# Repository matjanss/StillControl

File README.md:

# StillControl
Simple Arduino Nano based solid state relay control hardware and software

Repository will be updated intermittently.

Please refer to the "Hardware" folder for the PCB & license information, software folder contains a VSCode project.

https://youtu.be/iHSRMQVA5wc

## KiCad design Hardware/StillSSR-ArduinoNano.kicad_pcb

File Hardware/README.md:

# StillControl PCB v1.0
Simple Arduino Nano based solid state relay control hardware and software

---

The PCB is a relatively simple breakout board for an Arduino Nano, exposing a number of interfaces in JST PH (2.00mm) connectors and standard 2.54mm pin Headers:

- Footprint for an Arduino Nano V3 with (optional/additional) breakout pin row exposed.
- 3 potentiometers (with filter caps & resistor)
- 3 buffered and somewhat protected SSR outputs
- I2C for ie. display or other peripherals
- I2C header for a BMP388/390 barometer
- 1-Wire interface for temperature sensors
- Buzzer
- Error led connector
- On board 5V regulator, needs 9-12V

Repository will be updated when board is tested, updates to be done in v1.1
Hardware is licensed under Creative Commons NC BY SA.

JLCPCB Production files: StillSSR-Arduinonano.zip

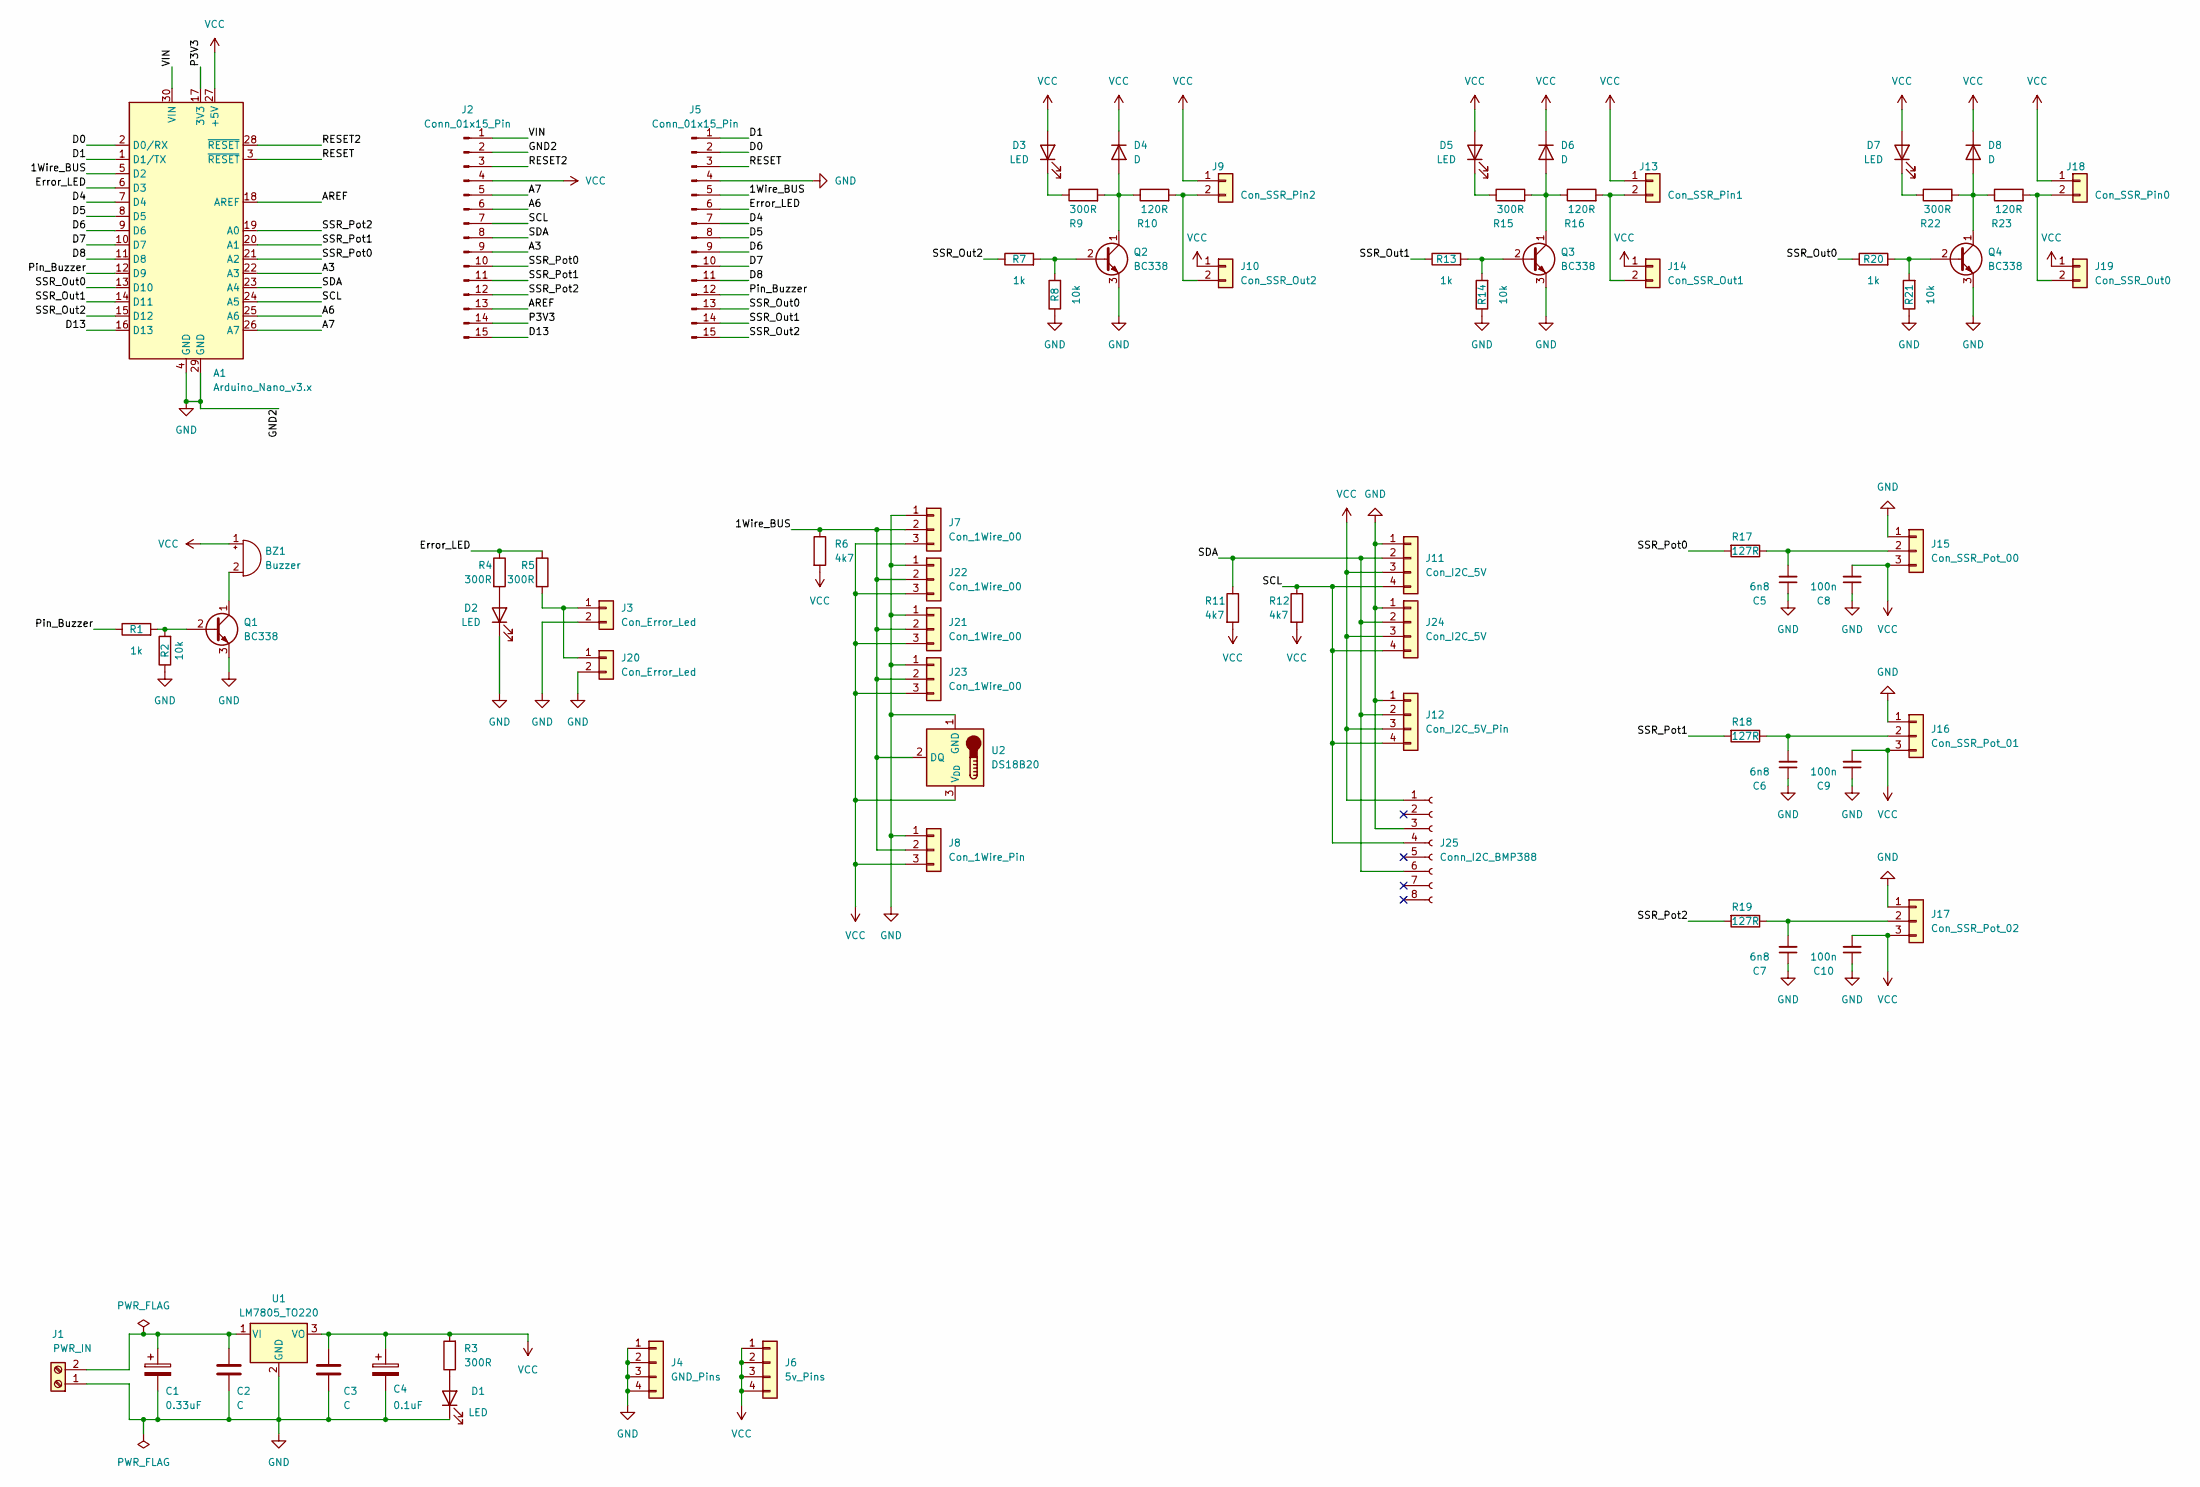
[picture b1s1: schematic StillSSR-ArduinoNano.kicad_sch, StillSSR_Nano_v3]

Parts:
A1: Arduino_Nano_v3.x; Arduino_Nano
BZ1: Buzzer; Buzzer_12x9.5RM7.6
C1: 0.33uF; CP_Radial_D5.0mm_P2.50mm
C2, C3: C; C_Rect_L4.0mm_W2.5mm_P2.50mm
C4: 0.1uF; CP_Radial_D5.0mm_P2.50mm
C5, C6, C7: 6n8; C_Rect_L4.0mm_W2.5mm_P2.50mm
C8, C9, C10: 100n; C_Rect_L4.0mm_W2.5mm_P2.50mm
D1, D2, D3, D5, D7: LED; LED_D3.0mm
D4, D6, D8: D; D_DO-34_SOD68_P7.62mm_Horizontal
J1: PWR_IN; TerminalBlock_bornier-2_P5.08mm
J2, J5: Conn_01x15_Pin; PinSocket_1x15_P2.54mm_Vertical
J3: Con_Error_Led; JST_PH_B2B-PH-K_1x02_P2.00mm_Vertical
J4: GND_Pins; PinHeader_1x04_P2.54mm_Vertical
J6: 5v_Pins; PinHeader_1x04_P2.54mm_Vertical
J7, J21, J22, J23: Con_1Wire_00; JST_PH_B3B-PH-K_1x03_P2.00mm_Vertical
J8: Con_1Wire_Pin; PinHeader_1x03_P2.54mm_Vertical
J9: Con_SSR_Pin2; PinHeader_1x02_P2.54mm_Vertical
J10: Con_SSR_Out2; JST_PH_B2B-PH-K_1x02_P2.00mm_Vertical
J11, J24: Con_I2C_5V; JST_PH_B4B-PH-K_1x04_P2.00mm_Vertical
J12: Con_I2C_5V_Pin; PinHeader_1x04_P2.54mm_Vertical
J13: Con_SSR_Pin1; PinHeader_1x02_P2.54mm_Vertical
J14: Con_SSR_Out1; JST_PH_B2B-PH-K_1x02_P2.00mm_Vertical
J15: Con_SSR_Pot_00; JST_PH_B3B-PH-K_1x03_P2.00mm_Vertical
J16: Con_SSR_Pot_01; JST_PH_B3B-PH-K_1x03_P2.00mm_Vertical
J17: Con_SSR_Pot_02; JST_PH_B3B-PH-K_1x03_P2.00mm_Vertical
J18: Con_SSR_Pin0; PinHeader_1x02_P2.54mm_Vertical
J19: Con_SSR_Out0; JST_PH_B2B-PH-K_1x02_P2.00mm_Vertical
J20: Con_Error_Led; PinHeader_1x02_P2.54mm_Vertical
J25: Conn_I2C_BMP388; PinSocket_1x08_P2.54mm_Vertical
Q1, Q2, Q3, Q4: BC338; TO-92_Inline
R1, R7, R13, R20: 1k; R_Axial_DIN0207_L6.3mm_D2.5mm_P7.62mm_Horizontal
R2, R8, R14, R21: 10k; R_Axial_DIN0207_L6.3mm_D2.5mm_P7.62mm_Horizontal
R3, R4, R5, R9, R15, R22: 300R; R_Axial_DIN0207_L6.3mm_D2.5mm_P7.62mm_Horizontal
R6, R11, R12: 4k7; R_Axial_DIN0207_L6.3mm_D2.5mm_P7.62mm_Horizontal
R10, R16, R23: 120R; R_Axial_DIN0207_L6.3mm_D2.5mm_P7.62mm_Horizontal
R17, R18, R19: 127R; R_Axial_DIN0207_L6.3mm_D2.5mm_P7.62mm_Horizontal
U1: LM7805_TO220; TO-220-3_Vertical
U2: DS18B20; TO-92_Inline

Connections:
/1Wire_BUS: A1.5 (D2), J5.5, J7.2, J8.2, J21.2, J22.2, J23.2, R6.1, U2.2 (DQ)
/A3: A1.22 (A3), J2.9
/A6: A1.25 (A6), J2.6
/A7: A1.26 (A7), J2.5
/AREF: A1.18 (AREF), J2.13
/D0: A1.2 (D0/RX), J5.2
/D1: A1.1 (D1/TX), J5.1
/D4: A1.7 (D4), J5.7
/D5: A1.8 (D5), J5.8
/D6: A1.9 (D6), J5.9
/D7: A1.10 (D7), J5.10
/D8: A1.11 (D8), J5.11
/D13: A1.16 (D13), J2.15
/Error_LED: A1.6 (D3), J5.6, R4.1, R5.1
/P3V3: A1.17 (3V3), J2.14
/Pin_Buzzer: A1.12 (D9), J5.12, R1.1
/RESET: A1.3 (~RESET), J5.3
/RESET2: A1.28 (~RESET), J2.3
/SCL: A1.24 (A5), J2.7, J11.4, J12.4, J24.4, J25.4, R12.1
/SDA: A1.23 (A4), J2.8, J11.2, J12.2, J24.2, J25.6, R11.1
/SSR_Out0: A1.13 (D10), J5.13, R20.1
/SSR_Out1: A1.14 (D11), J5.14, R13.1
/SSR_Out2: A1.15 (D12), J5.15, R7.1
/SSR_Pot0: A1.21 (A2), J2.10, R17.2
/SSR_Pot1: A1.20 (A1), J2.11, R18.2
/SSR_Pot2: A1.19 (A0), J2.12, R19.2
/VIN: A1.30 (VIN), J2.1
GND: A1.4 (GND), A1.29 (GND), C1.2, C2.2, C3.2, C4.2, C5.1, C6.1, C7.1, C8.1, C9.1, C10.1, D1.1 (K), D2.1 (K), J1.1, J2.2, J3.2, J4.1, J4.2, J4.3, J4.4, J5.4, J7.1, J8.1, J11.1, J12.1, J15.1, J16.1, J17.1, J20.2, J21.1, J22.1, J23.1, J24.1, J25.3, Q1.3 (E), Q2.3 (E), Q3.3 (E), Q4.3 (E), R2.1, R8.1, R14.1, R21.1, U1.2 (GND), U2.1 (GND)
unnamed: BZ1.2 (+), Q1.1 (C)
unnamed: D1.2 (A), R3.1
unnamed: D2.2 (A), R4.2
unnamed: D3.1 (K), R9.1
unnamed: D4.2 (A), Q2.1 (C), R9.2, R10.1
unnamed: D5.1 (K), R15.1
unnamed: D6.2 (A), Q3.1 (C), R15.2, R16.1
unnamed: D7.1 (K), R22.1
unnamed: D8.2 (A), Q4.1 (C), R22.2, R23.1
unnamed: C1.1, C2.1, J1.2, U1.1 (VI)
unnamed: J9.2, J10.2, R10.2
unnamed: J13.2, J14.2, R16.2
unnamed: C5.2, J15.2, R17.1
unnamed: C6.2, J16.2, R18.1
unnamed: C7.2, J17.2, R19.1
unnamed: J18.2, J19.2, R23.2
unnamed: J3.1, J20.1, R5.2
unnamed: Q1.2 (B), R1.2, R2.2
unnamed: Q2.2 (B), R7.2, R8.2
unnamed: Q3.2 (B), R13.2, R14.2
unnamed: Q4.2 (B), R20.2, R21.2
VCC: A1.27 (+5V), BZ1.1 (-), C3.1, C4.1, C8.2, C9.2, C10.2, D3.2 (A), D4.1 (K), D5.2 (A), D6.1 (K), D7.2 (A), D8.1 (K), J2.4, J6.1, J6.2, J6.3, J6.4, J7.3, J8.3, J9.1, J10.1, J11.3, J12.3, J13.1, J14.1, J15.3, J16.3, J17.3, J18.1, J19.1, J21.3, J22.3, J23.3, J24.3, J25.1, R3.2, R6.2, R11.2, R12.2, U1.3 (VO), U2.3 (V_{DD})

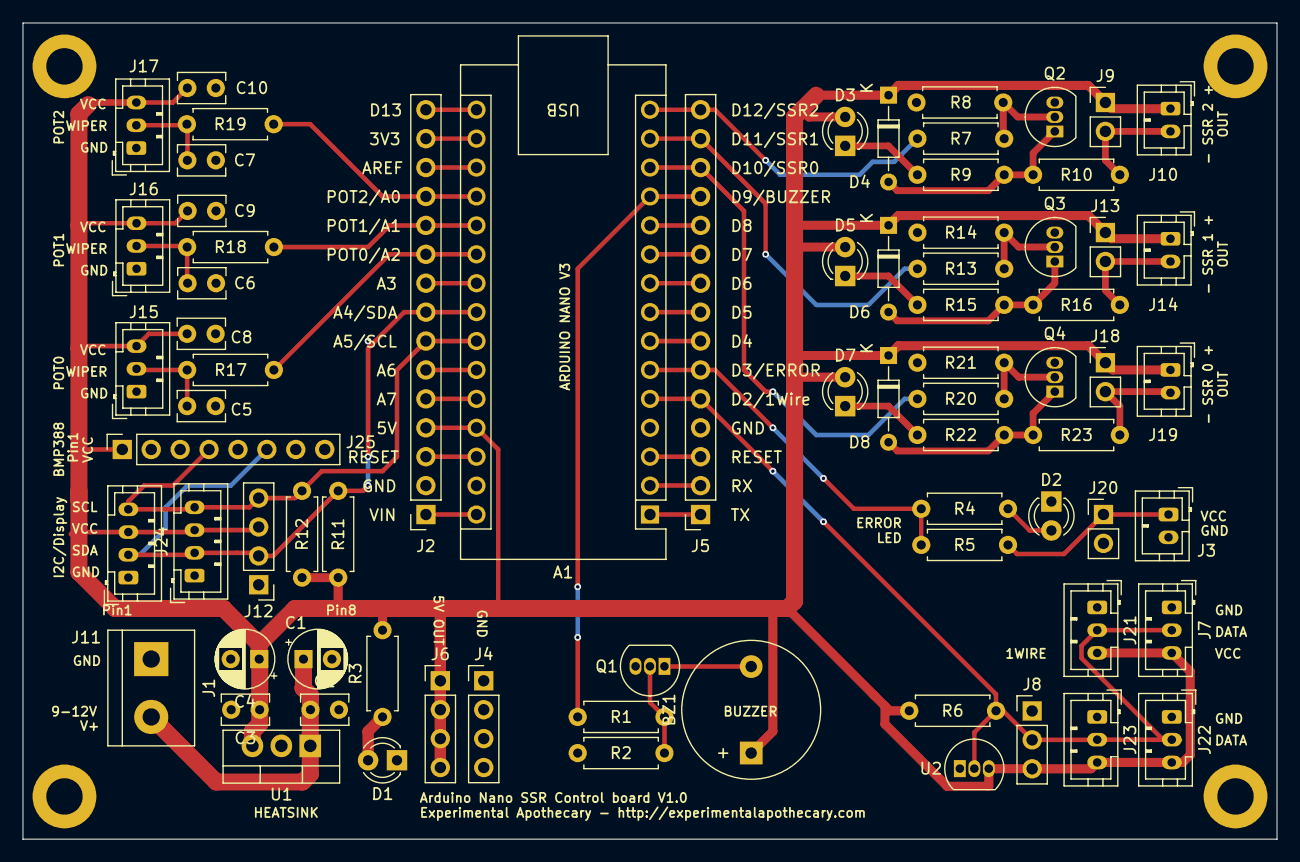
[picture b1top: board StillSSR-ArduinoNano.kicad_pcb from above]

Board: 2 copper layers, 110.2 x 71.7 mm, 74 parts (0 on the bottom side), 50 nets.

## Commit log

2023-10-05 Updated readme's
2023-10-05 Add files via upload
    Upload v1.0 of JLCPCB gerber files
2023-10-05 Kicad schematics added
2023-11-16 Upload v1.0 software

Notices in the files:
Hardware/StillSSR-ArduinoNano.kicad_pcb:
© 2023 - Experimental Apothecary
LICENSE: Creative Commons CC BY-NC-SA
https://creativecommons.org/licenses/by-nc-sa/4.0
